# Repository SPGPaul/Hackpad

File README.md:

# Hackpad

Welcome to my Hackpad project!

My first time using KiCAD but i hope i did a good job :)

---

## Bill of Materials (BOM)

| Qty | Part                   |
|-----|------------------------|
|  4  | Cherry MX Switches     |
|  2  | SK6812 MINI LEDs       |
|  1  | XIAO RP2040            |
|  4  | Blank DSA Keycaps      |
|  4  | M3x16 Bolt             |
|  4  | M3 Heatset             |
|  1  | EC11 Rotary Encoder    |

---

## Images

### Assembly

### PCB

### Case

### Schematic

---

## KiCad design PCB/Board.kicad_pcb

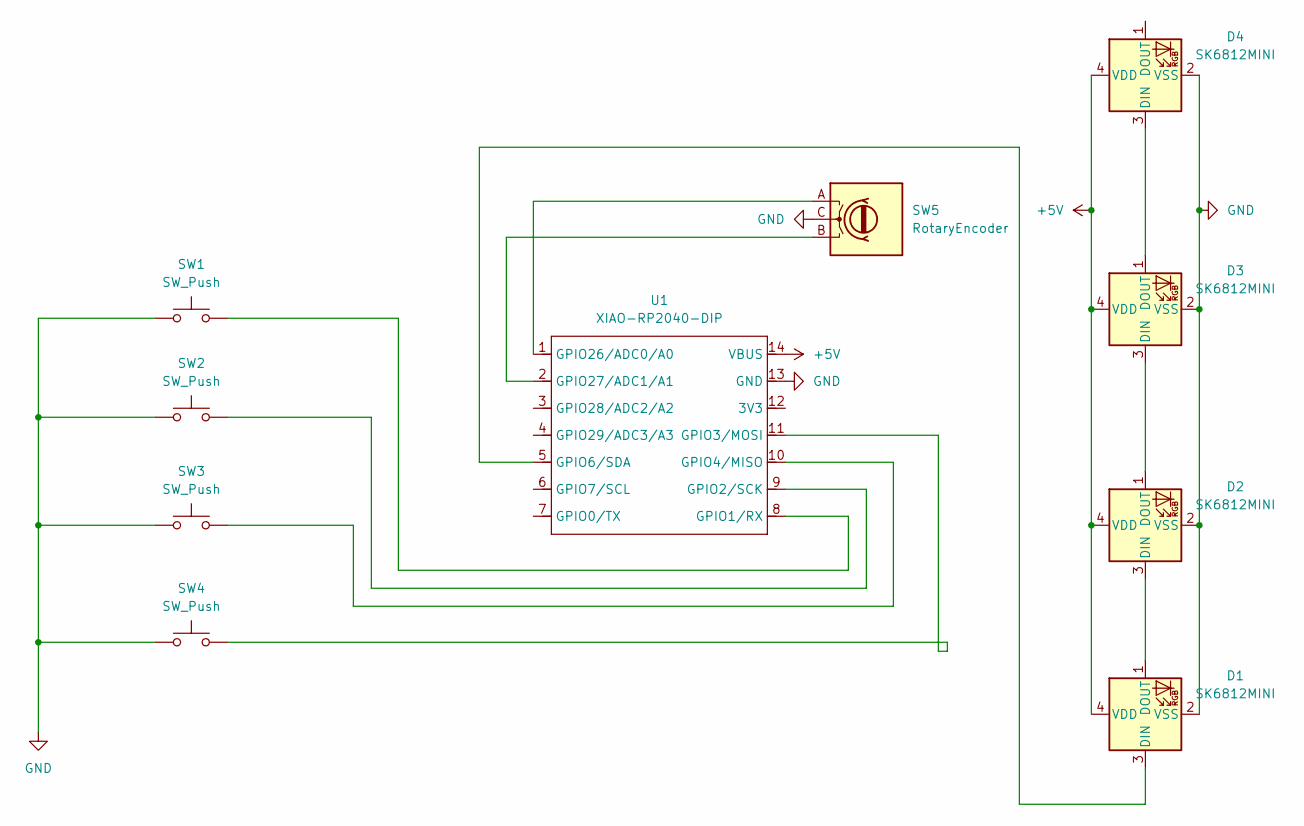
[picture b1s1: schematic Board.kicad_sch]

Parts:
D1, D2, D3, D4: SK6812MINI; LED_SK6812MINI_PLCC4_3.5x3.5mm_P1.75mm
SW1, SW2, SW3, SW4: SW_Push; SW_Cherry_MX_1.00u_PCB
SW5: RotaryEncoder; RotaryEncoder_Alps_EC11E-Switch_Vertical_H20mm
U1: XIAO-RP2040-DIP

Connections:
+5V: D1.4 (VDD), D2.4 (VDD), D3.4 (VDD), D4.4 (VDD), U1.14 (VBUS)
GND: D1.2 (VSS), D2.2 (VSS), D3.2 (VSS), D4.2 (VSS), SW1.1, SW2.1, SW3.1, SW4.1, SW5.C, U1.13 (GND)
unnamed: D1.3 (DIN), U1.5 (GPIO6/SDA)
unnamed: D1.1 (DOUT), D2.3 (DIN)
unnamed: D2.1 (DOUT), D3.3 (DIN)
unnamed: D3.1 (DOUT), D4.3 (DIN)
unnamed: SW1.2, U1.8 (GPIO1/RX)
unnamed: SW2.2, U1.9 (GPIO2/SCK)
unnamed: SW4.2, U1.11 (GPIO3/MOSI)
unnamed: SW3.2, U1.10 (GPIO4/MISO)
unnamed: SW5.A, U1.1 (GPIO26/ADC0/A0)
unnamed: SW5.B, U1.2 (GPIO27/ADC1/A1)

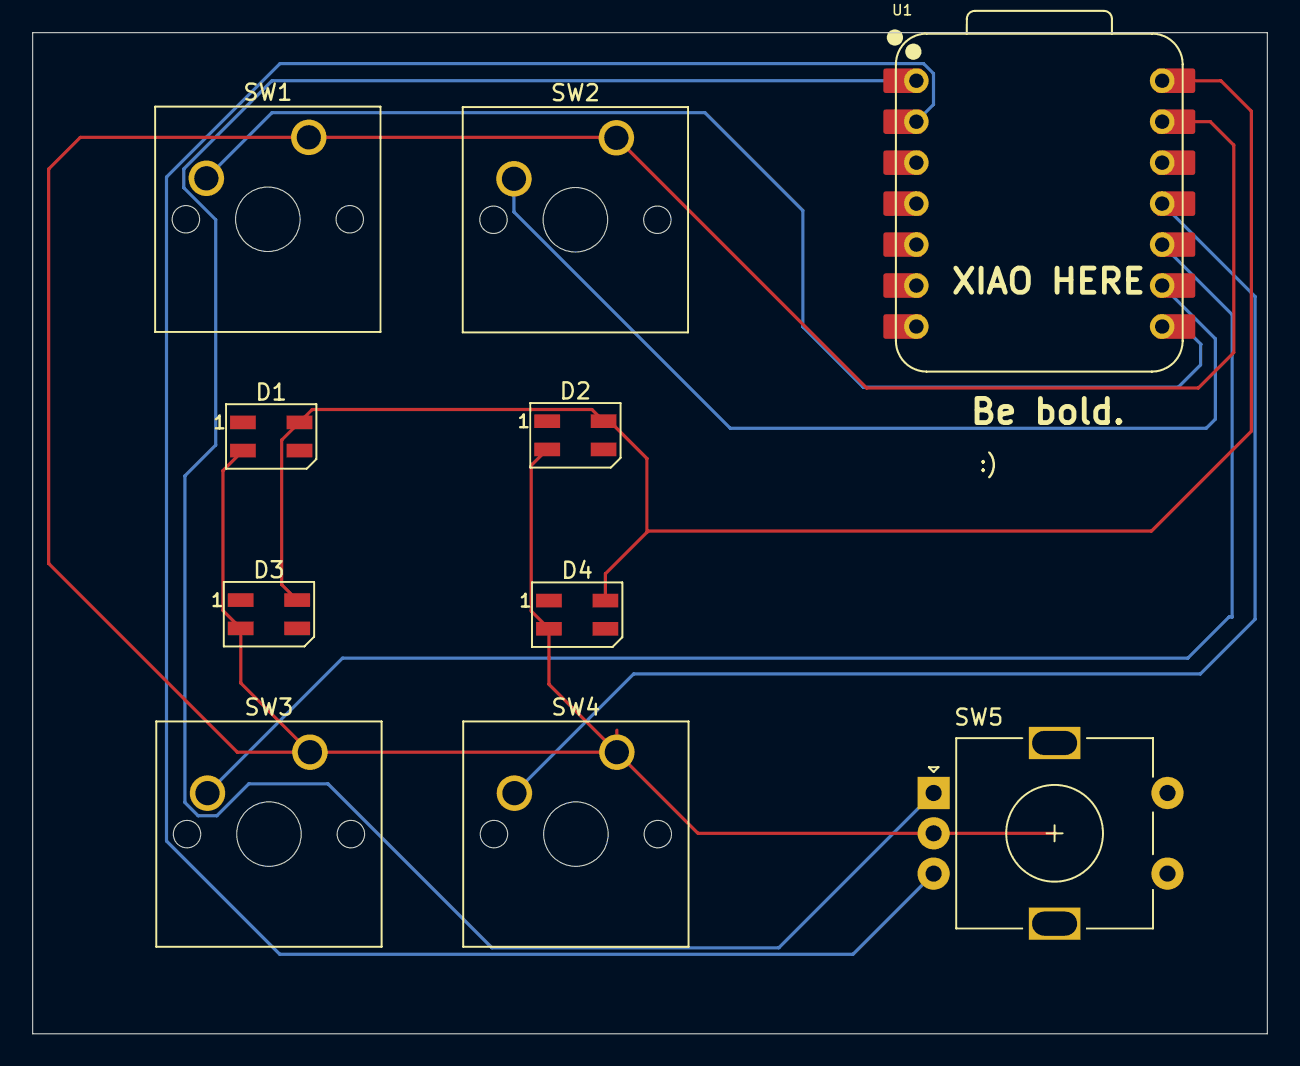
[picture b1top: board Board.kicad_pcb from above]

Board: 2 copper layers, 76.5 x 62.1 mm, 10 parts (0 on the bottom side), 12 nets.

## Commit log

2025-12-06 added kicad files
2025-12-06 added cad
2025-12-06 added firmware
2025-12-06 Revise README by removing initial content
    Removed initial description and BOM list.
2025-12-08 updated pcb text
